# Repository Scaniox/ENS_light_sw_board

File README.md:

A simple breakout board with 4 LEDs and 4 Buttons, designed to help for the ELEC3227 embedded networks coursework.
component choices are so that it is as cheap as possible from JLC PCB's PCBA service

Also see the AVR C library to to interface with it easily: https://github.com/Scaniox/ENS_light_sw_board_C_library

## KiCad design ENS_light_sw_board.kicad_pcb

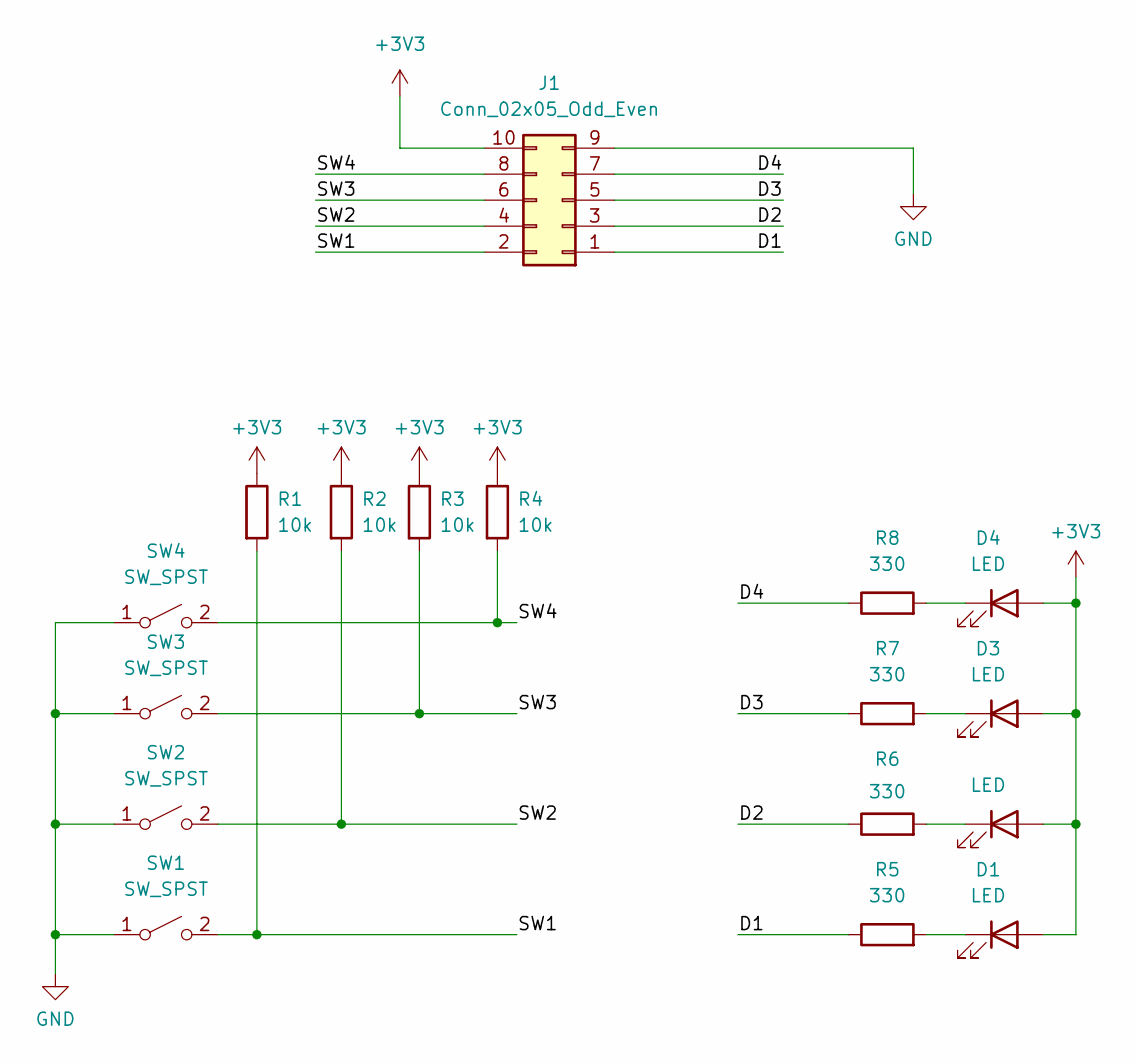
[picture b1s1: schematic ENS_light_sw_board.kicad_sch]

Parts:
D1, D2, D3, D4: LED; LED_0805_2012Metric_Pad1.15x1.40mm_HandSolder
J1: Conn_02x05_Odd_Even; PinHeader_2x05_P2.54mm_Vertical
R1, R2, R3, R4: 10k; R_0805_2012Metric_Pad1.20x1.40mm_HandSolder
R5, R6, R7, R8: 330; R_0805_2012Metric_Pad1.20x1.40mm_HandSolder
SW1, SW2, SW3, SW4: SW_SPST; SW_Push_1P1T_XKB_TS-1187A

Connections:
+3V3: D1.2 (A), D2.2 (A), D3.2 (A), D4.2 (A), J1.10, R1.1, R2.1, R3.1, R4.1
/D1: J1.1, R5.1
/D2: J1.3, R6.1
/D3: J1.5, R7.1
/D4: J1.7, R8.1
/SW1: J1.2, R1.2, SW1.2 (B)
/SW2: J1.4, R2.2, SW2.2 (B)
/SW3: J1.6, R3.2, SW3.2 (B)
/SW4: J1.8, R4.2, SW4.2 (B)
GND: J1.9, SW1.1 (A), SW2.1 (A), SW3.1 (A), SW4.1 (A)
unnamed: D1.1 (K), R5.2
unnamed: D2.1 (K), R6.2
unnamed: D3.1 (K), R7.2
unnamed: D4.1 (K), R8.2

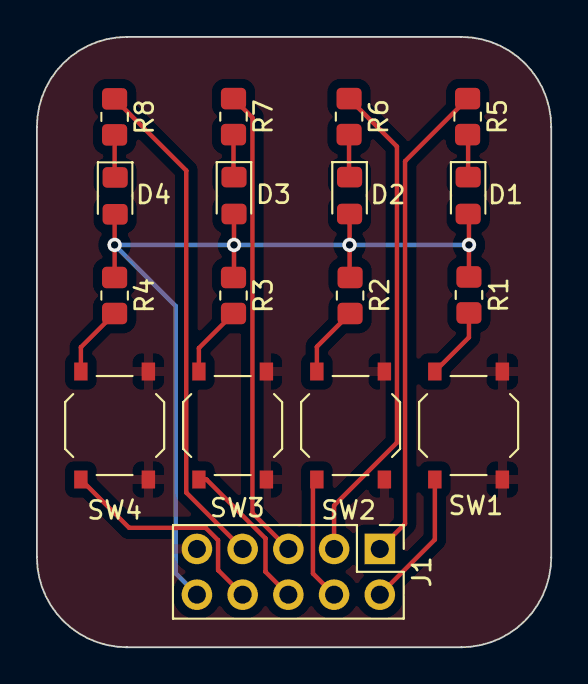
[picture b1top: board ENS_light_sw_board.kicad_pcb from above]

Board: 2 copper layers, 28.6 x 33.9 mm, 17 parts (0 on the bottom side), 14 nets.

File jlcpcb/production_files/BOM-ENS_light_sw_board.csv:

Comment,Designator,Footprint,LCSC,Quantity
10k,"R1,R2,R3,R4",R_0805_2012Metric_Pad1.20x1.40mm_HandSolder,C17414,4
330,"R5,R6,R7,R8",R_0805_2012Metric_Pad1.20x1.40mm_HandSolder,C17630,4
LED,"D1,D2,D3,D4",LED_0805_2012Metric_Pad1.15x1.40mm_HandSolder,C2296,4
SW_SPST,"SW1,SW2,SW3,SW4",SW_Push_1P1T_XKB_TS-1187A,C318884,4

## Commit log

2024-11-16 init
2024-11-17 prod v1
2025-01-05 image
